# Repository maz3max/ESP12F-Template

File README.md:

# ESP-12F Board

This KiCAD project template is the basis of a board integrating the ESP-12F Board from AI Thinker.

This template includes the basic schematic (and routing) needed to integrate this module in your own PCB design.

Look at this beautiful pinout sourced from: [Acrobotics web page](https://acrobotic.com/products/acr-00021)

(c)2019 Maximilian Deubel

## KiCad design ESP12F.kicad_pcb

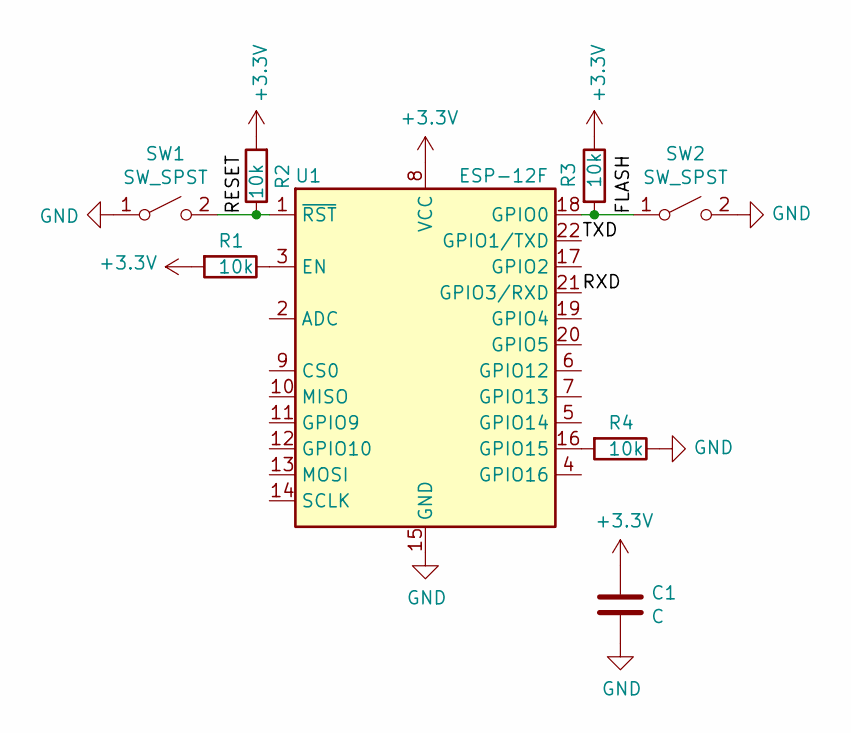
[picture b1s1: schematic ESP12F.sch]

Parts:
C1: C; C_0603_1608Metric_Pad1.05x0.95mm_HandSolder
R1, R2, R3, R4: 10k; R_0603_1608Metric_Pad1.05x0.95mm_HandSolder
SW1, SW2: SW_SPST; SolderJumper-2_P1.3mm_Open_TrianglePad1.0x1.5mm
U1: ESP-12F; ESP-12E

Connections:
+3V3: C1.1, R1.2, R2.2, R3.1, U1.8 (VCC)
/FLASH: R3.2, SW2.1 (A), U1.18 (GPIO0)
/RESET: R2.1, SW1.2 (B), U1.1 (~RST)
/RXD: U1.21 (GPIO3/RXD)
/TXD: U1.22 (GPIO1/TXD)
GND: C1.2, R4.1, SW1.1 (A), SW2.2 (B), U1.15 (GND)
unnamed: R1.1, U1.3 (EN)
unnamed: R4.2, U1.16 (GPIO15)

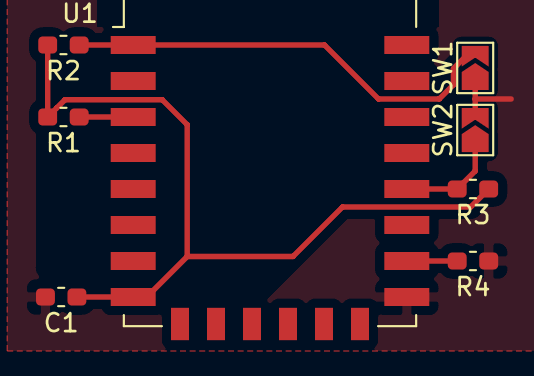
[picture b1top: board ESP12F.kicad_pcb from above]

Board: 2 copper layers, 8 parts (0 on the bottom side), 6 nets.

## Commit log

2019-04-20 add README and meta data
